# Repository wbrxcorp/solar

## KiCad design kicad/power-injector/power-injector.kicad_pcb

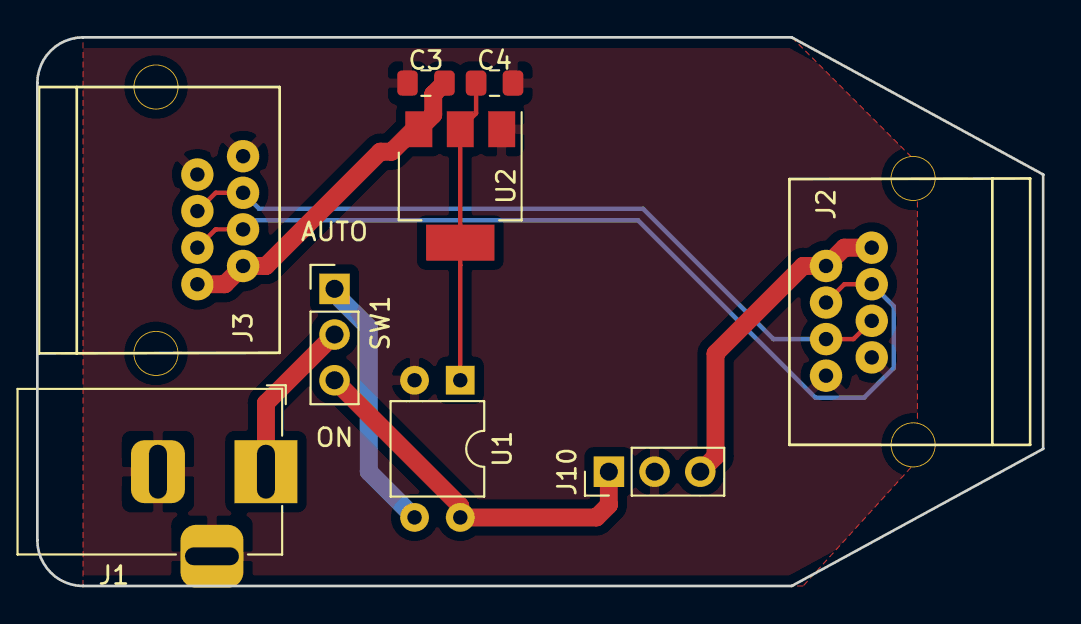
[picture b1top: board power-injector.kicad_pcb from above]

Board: 2 copper layers, 55.9 x 30.5 mm, 9 parts (0 on the bottom side), 9 nets.

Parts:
C3, C4: 0.1uF; C_0805_2012Metric_Pad1.15x1.40mm_HandSolder
J1: Barrel_Jack_Switch; BarrelJack_Horizontal
J2, J3: RJ45
J10: DCDC; PinHeader_1x03_P2.54mm_Vertical
SW1: SW_SPDT; PinHeader_1x03_P2.54mm_Vertical
U1: TLP222A; DIP-4_W7.62mm
U2: AMS1117-1.2; SOT-223-3_TabPin2

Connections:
/1V2: C4.1, U1.1, U2.2
/5V: J2.1, J2.2, J10.3
/A: J2.5, J2.6, J3.5, J3.6
/B: J2.3, J2.4, J3.3, J3.4
/VBATT: J10.1, SW1.3, U1.4
/VBATT_AUTO: SW1.1, U1.3
/VBATT_IN: J1.1, SW1.2
/VCTRLR: C3.1, J3.1, J3.2, U2.3
GND: C3.2, C4.2, J1.2, J1.3, J2.7, J2.8, J3.7, J3.8, J10.2, U1.2, U2.1

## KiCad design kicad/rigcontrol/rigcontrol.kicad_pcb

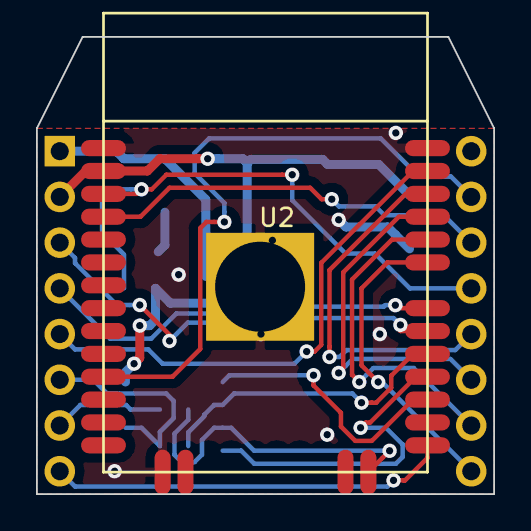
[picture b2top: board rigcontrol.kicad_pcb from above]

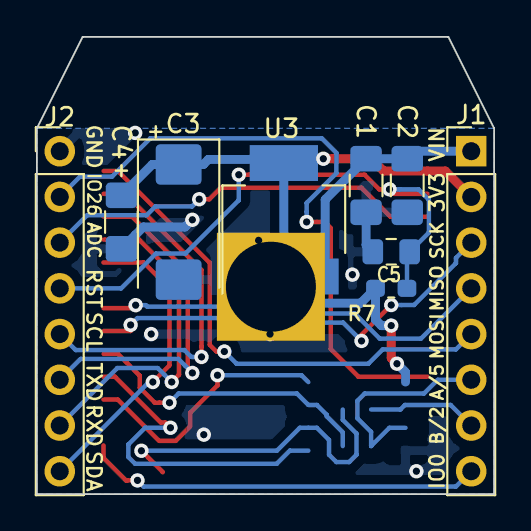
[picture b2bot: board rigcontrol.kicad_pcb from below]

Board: 2 copper layers, 25.4 x 25.4 mm, 10 parts (9 on the bottom side), 13 nets.

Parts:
C1, C2, C4: C; C_1206_3216Metric_Pad1.42x1.75mm_HandSolder
C3: C; CP_EIA-7343-15_Kemet-W_Pad2.25x2.55mm_HandSolder
C5: 1uF; C_0805_2012Metric_Pad1.15x1.40mm_HandSolder
J1, J2: Conn_01x08; PinHeader_1x08_P2.54mm_Vertical
R7: 10K; R_0603_1608Metric_Pad1.05x0.95mm_HandSolder
U2: ESP-WROOM-32; ESP32-WROOM
U3: AMS1117-3.3; SOT-223-3_TabPin2

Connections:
+3V3: C3.1, C4.1, J1.2, R7.1, U2.2, U3.2
GND: C1.2, C2.2, C3.2, C4.2, C5.2, J2.1, U2.1, U2.15, U2.38, U2.39, U3.1
IO0: J1.8, U2.25
IO26: J2.2, U2.11
MISO: J1.4, U2.31
MOSI: J1.5, U2.37
RST: C5.1, J2.4, R7.2, U2.3
RXD: J2.7, U2.34
SCK: J1.3, U2.30
SCL: J2.5, U2.36
SDA: J2.8, U2.33
TXD: J2.6, U2.35
VCC: C1.1, C2.1, J1.1, U3.3

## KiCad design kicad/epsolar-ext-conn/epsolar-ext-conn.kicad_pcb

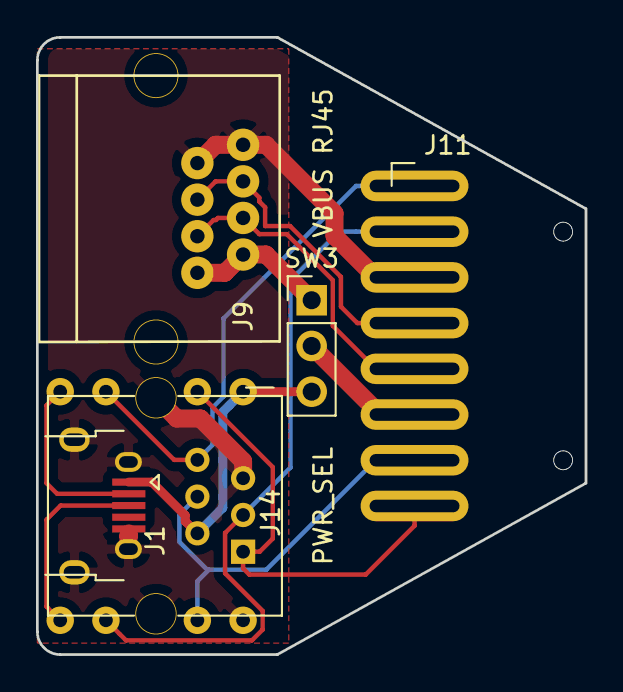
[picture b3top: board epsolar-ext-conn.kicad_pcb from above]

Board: 2 copper layers, 30.5 x 34.3 mm, 5 parts (0 on the bottom side), 12 nets.

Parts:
J1: USB_B_Micro; USB_Micro-B_Horizontal
J9: RJ45
J11: CONN; 8p_cable_holes
J14: USBSERIAL; usbserial
SW3: SW_SPDT; PinHeader_1x03_P2.54mm_Vertical

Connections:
/A: J9.5, J9.6, J11.4
/B: J9.3, J9.4, J11.5
/D+: J1.3, J14.7
/D-: J1.2, J14.8
/IO0: J11.1, J14.6
/RESET: J11.8, J14.1
/RXD: J11.2, J14.3
/TXD: J11.7, J14.4
/VBUS: J1.1, J14.2, SW3.3
/VCTRLR: J9.1, J9.2, SW3.1
/VIN: J11.6, SW3.2
GND: J1.5, J1.6, J9.7, J9.8, J11.3, J14.5

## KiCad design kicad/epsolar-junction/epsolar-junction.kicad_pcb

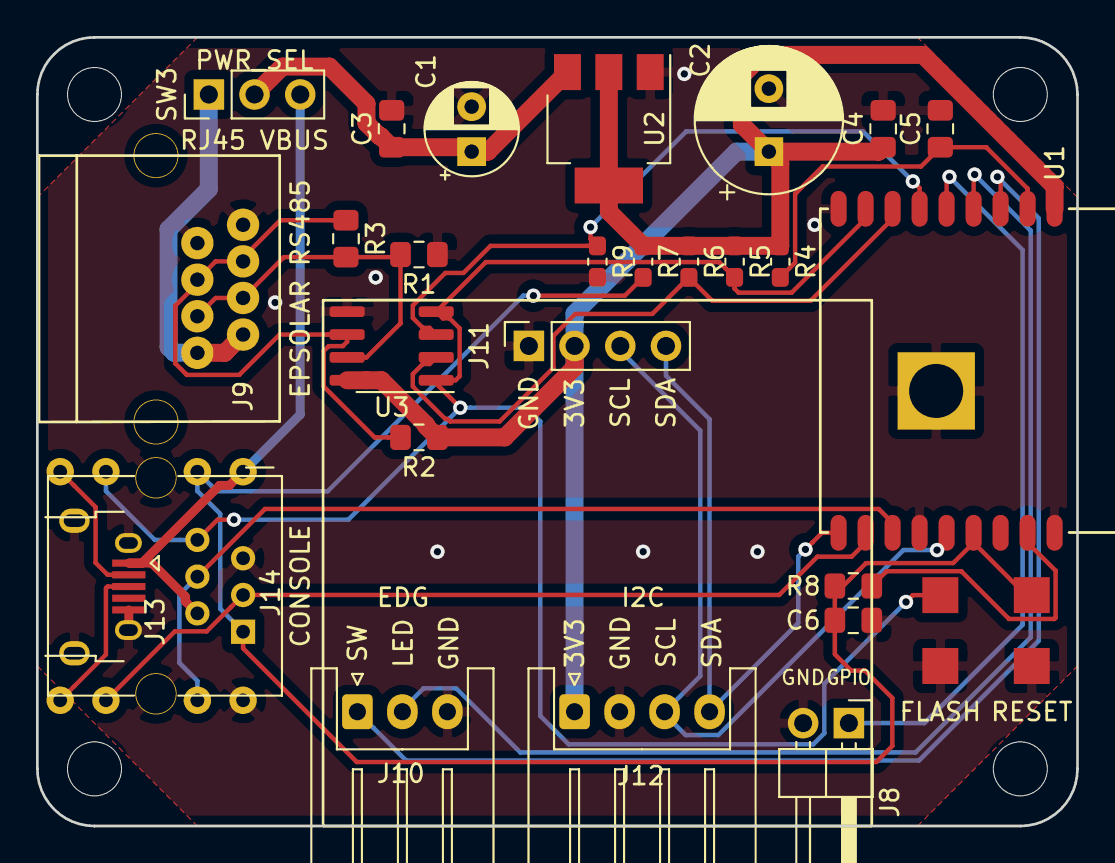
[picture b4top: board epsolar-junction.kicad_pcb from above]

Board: 2 copper layers, 57.8 x 43.8 mm, 28 parts (0 on the bottom side), 22 nets.

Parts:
C1: 100uF; CP_Radial_D5.0mm_P2.50mm
C2: 1000uF; CP_Radial_D8.0mm_P3.50mm
C3, C4, C5, C6: 0.1uF; C_0805_2012Metric_Pad1.15x1.40mm_HandSolder
J8: Conn_01x02; PinHeader_1x02_P2.54mm_Horizontal
J9: RJ45
J10: EDG; JST_XH_S3B-XH-A_1x03_P2.50mm_Horizontal
J11: DISPLAY; PinSocket_1x04_P2.54mm_Vertical
J12: I2C; JST_XH_S4B-XH-A_1x04_P2.50mm_Horizontal
J13: USB_B_Micro; USB_Micro-B_Horizontal
J14: USBSERIAL; usbserial
R1, R2: 20K; R_0805_2012Metric_Pad1.15x1.40mm_HandSolder
R3: 200; R_0805_2012Metric_Pad1.15x1.40mm_HandSolder
R4, R5, R6, R7, R9: 10K; R_0603_1608Metric_Pad1.05x0.95mm_HandSolder
R8: 470; R_0805_2012Metric_Pad1.15x1.40mm_HandSolder
SW1, SW2: SW_Push; tactile_switch_smd_4x3mm_2p
SW3: SW_SPDT; PinHeader_1x03_P2.54mm_Vertical
U1: ESP-13-WROOM-02
U2: AMS1117-3.3; SOT-223-3_TabPin2
U3: MAX3485; SOIC-8_3.9x4.9mm_P1.27mm

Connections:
/3V3: C2.1, C4.1, J11.2, J12.1, R2.1, R4.1, R5.1, R6.1, R7.1, U1.1, U2.2, U3.8
/A: J9.5, J9.6, R2.2, R3.1, U3.6
/B: J9.3, J9.4, R1.2, R3.2, U3.7
/D+: J13.3, J14.7
/D-: J13.2, J14.8
/EDG_LED: J10.2, U1.4
/EDG_SW: J10.1, U1.3
/EN: C5.1, R4.2, U1.2
/GPIO: J8.1, U1.5
/IO0: J14.6, R5.2, SW2.1, U1.8, U3.1, U3.4
/IO2: R6.2, U1.7, U3.2
/IO15: R9.1, U1.6, U3.3
/RESET: C6.1, J14.1, R7.2, R8.2, SW1.1, U1.15
/RXD: J14.3, U1.11
/SCL: J11.3, J12.3, U1.14
/SDA: J11.4, J12.4, U1.10
/TXD: J14.4, U1.12
/VBUS: J13.1, J14.2, SW3.3
/VCTRLR: J9.1, J9.2, SW3.1
/VIN: C1.1, C3.1, SW3.2, U2.3
/WAKE: R8.1, U1.17
GND: C1.2, C2.2, C3.2, C4.2, C5.2, C6.2, J8.2, J9.7, J9.8, J10.3, J11.1, J12.2, J13.5, J13.6, J14.5, R1.1, R9.2, SW1.2, SW2.2, U1.9, U1.13, U1.18, U1.PAD, U2.1, U3.5

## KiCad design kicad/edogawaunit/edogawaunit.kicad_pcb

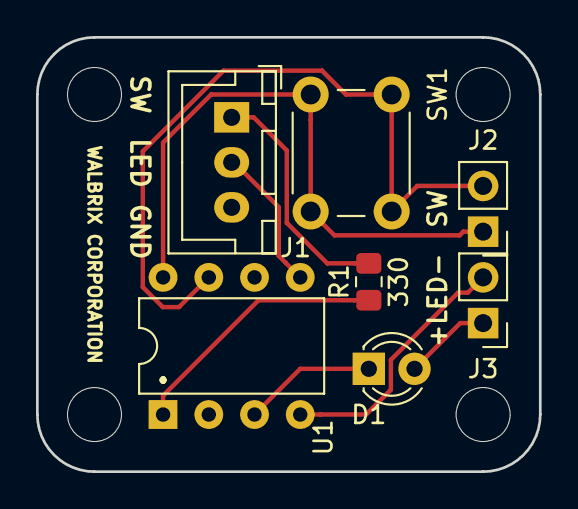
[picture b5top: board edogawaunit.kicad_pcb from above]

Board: 2 copper layers, 27.9 x 24.1 mm, 7 parts (0 on the bottom side), 9 nets.

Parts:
D1: LED; LED_D3.0mm
J1: Conn_01x03; JST_XH_B03B-XH-A_1x03_P2.50mm_Vertical
J2, J3: Conn_01x02; PinHeader_1x02_P2.54mm_Vertical
R1: 330; R_0805_2012Metric_Pad1.15x1.40mm_HandSolder
SW1: SW_Push; SW_PUSH_6mm
U1: TLP222A-2; DIP-8_W7.62mm

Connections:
/LEDMINUS: J3.2, U1.4
/LEDPLUS: D1.2, J3.1
/LED_IN: J1.2, U1.5
/SW1: J2.1, SW1.2, U1.8
/SW2: J2.2, SW1.1, U1.7
/SW_OUT: J1.1, R1.2
GND: J1.3, U1.2, U1.6
unnamed: D1.1, U1.3
unnamed: R1.1, U1.1

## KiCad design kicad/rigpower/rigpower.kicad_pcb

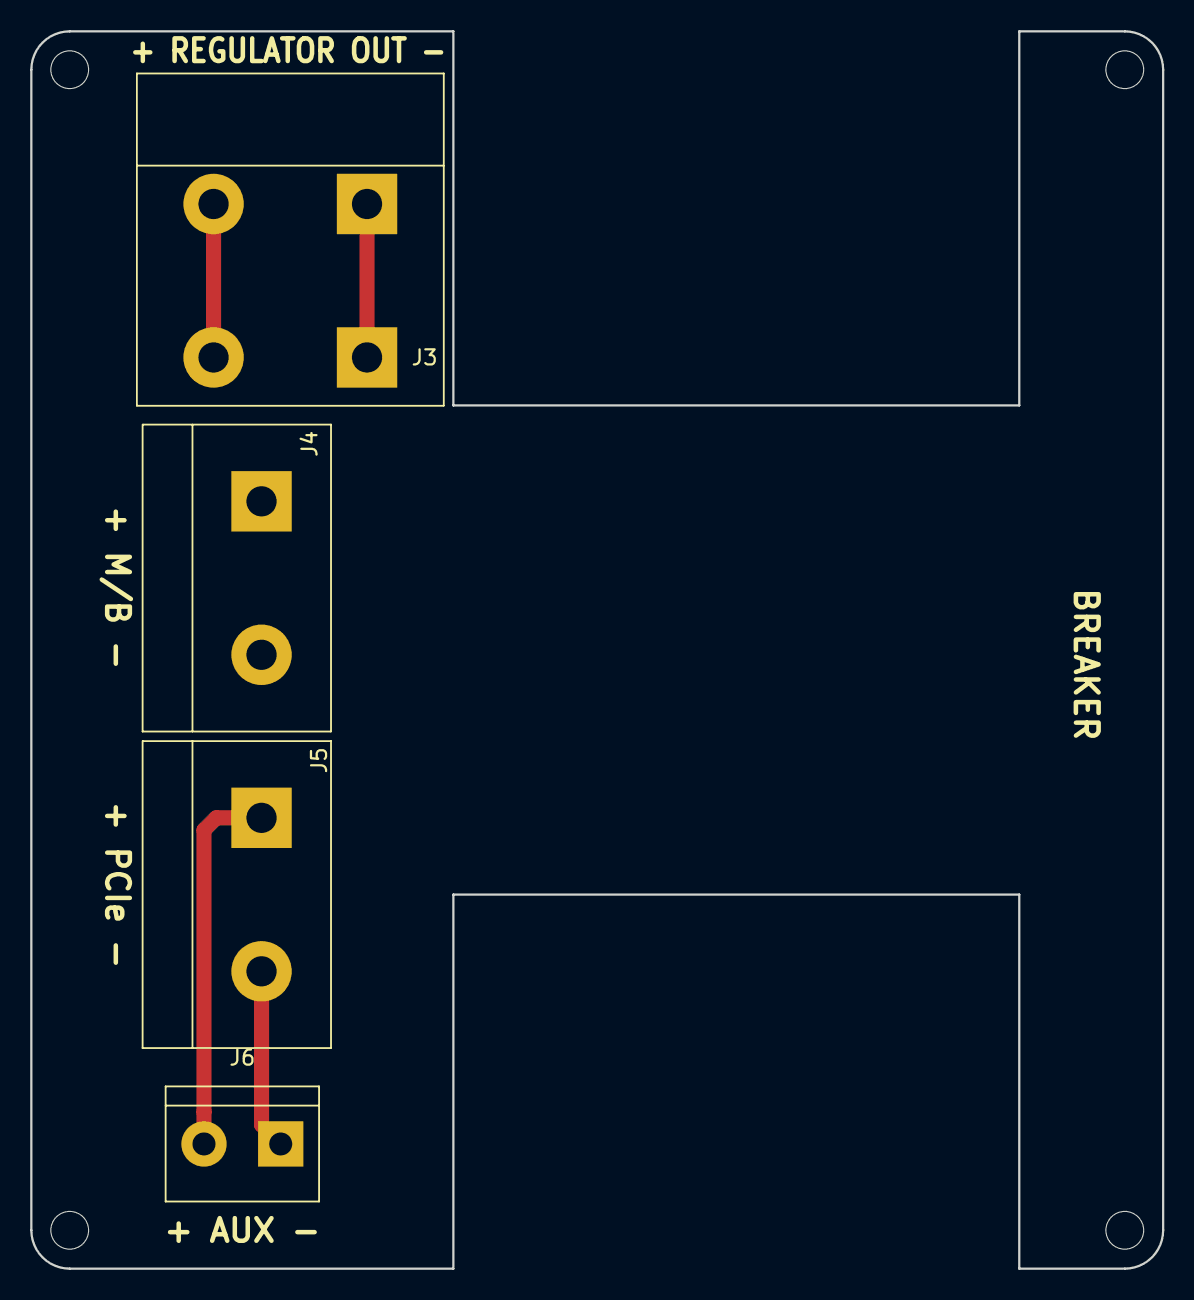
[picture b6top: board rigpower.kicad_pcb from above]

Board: 2 copper layers, 74.9 x 81.9 mm, 4 parts (0 on the bottom side), 2 nets.

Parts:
J3: Conn_01x02; TerminalBlock_P10.16mm
J4, J5: Conn_01x02; TerminalBlock_P9.5mm
J6: Conn_01x02; TerminalBlock_bornier-2_P5.08mm

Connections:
unnamed: J5.1, J6.2
unnamed: J5.2, J6.1

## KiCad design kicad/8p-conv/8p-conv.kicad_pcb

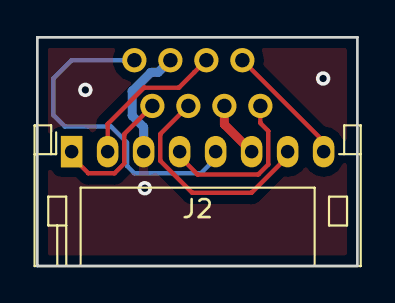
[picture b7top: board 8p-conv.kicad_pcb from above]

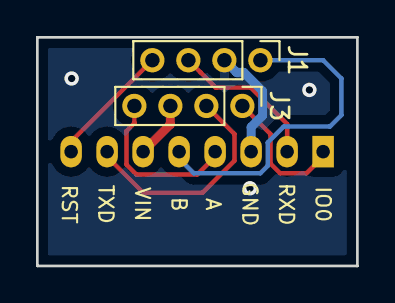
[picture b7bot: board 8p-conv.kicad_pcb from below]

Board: 2 copper layers, 17.8 x 12.7 mm, 3 parts (2 on the bottom side), 8 nets.

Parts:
J1, J3: Conn_01x04; PinHeader_1x04_P2.00mm_Vertical
J2: Conn_01x08; JST_PH_S8B-PH-K_1x08_P2.00mm_Horizontal

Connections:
/A: J2.4, J3.4
/B: J1.1, J2.5
/GND: J1.2, J2.3
/IO0: J2.1, J3.1
/RST: J1.4, J2.8
/RXD: J1.3, J2.2
/TXD: J2.7, J3.2
/VIN: J2.6, J3.3

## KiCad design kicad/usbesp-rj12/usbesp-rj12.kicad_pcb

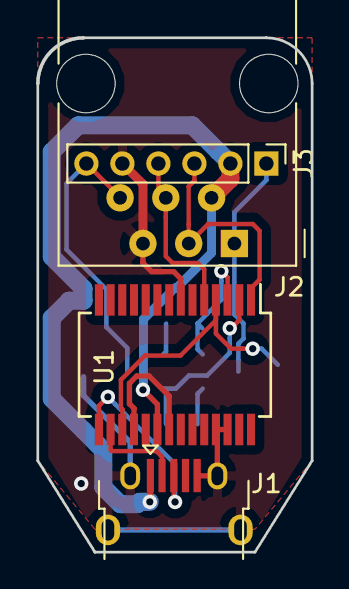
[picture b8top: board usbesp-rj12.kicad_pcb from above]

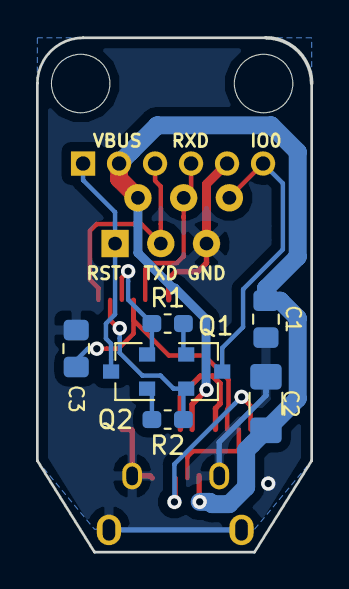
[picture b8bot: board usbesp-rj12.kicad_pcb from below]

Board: 2 copper layers, 15.2 x 28.6 mm, 11 parts (7 on the bottom side), 13 nets.

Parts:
C1, C3: 0.1uF; C_0805_2012Metric_Pad1.15x1.40mm_HandSolder
C2: 10uF; C_1206_3216Metric_Pad1.42x1.75mm_HandSolder
J1: USB_B_Micro; USB_Micro-B_Horizontal
J2: RJ12; RJ12_Amphenol_54601
J3: Conn_01x06; PinHeader_1x06_P2.00mm_Vertical
Q1, Q2: S9013; SOT-23
R1, R2: 10K; R_0603_1608Metric_Pad1.05x0.95mm_HandSolder
U1: FT232RL; SSOP-28_5.3x10.2mm_P0.65mm

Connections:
/3v3: C3.1, U1.4, U1.17
/DTR: Q1.2, R2.1, U1.2
/IO0: J2.6, J3.6, Q1.3
/RESET: J2.1, J3.1, Q2.3
/RTS: Q2.2, R1.1, U1.3
/RXD: J2.4, J3.4, U1.5
/TXD: J2.3, J3.3, U1.1
/USBDM: J1.2, U1.16
/USBDP: J1.3, U1.15
/VBUS: C1.1, C2.1, J1.1, J2.2, J3.2, U1.20
GND: C1.2, C2.2, C3.2, J1.5, J1.6, J2.5, J3.5, U1.7, U1.18, U1.21, U1.25, U1.26
unnamed: Q1.1, R1.2
unnamed: Q2.1, R2.2

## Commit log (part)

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2017-08-15 initial
2017-08-15 add poll script
2017-08-18 pyeptracer code adopted
2017-08-18 save to db functionality added
2017-08-18 ignore .txt files
2017-08-18 change 5min avg line color
2017-08-19 legend added
2017-08-21 possibility to specify output path
2017-08-24 set battery voltage y axis limits
2017-08-25 adjust legend text
2017-08-25 pymodbus adopted
2017-08-26 adjust battery voltage yaxis upper limit
2017-08-26 email_graph script added
2017-09-26 schema changed to store loads
2017-09-26 graph improved
2017-09-26 setparam utility added
2017-09-26 add 12v line
2017-10-06 htdocs added
2017-10-06 charset specified
2017-10-07 show usdjpy
2017-10-08 use yahoo api to get jpyusd
2017-10-09 a mandatory arg was missing
2017-10-13 coins.json format changed
2017-10-14 refresh functionality implemented
2017-10-14 btc price added
2017-10-14 refresh improved
2017-10-14 IoT server
2017-10-15 faster query using temporary table
2017-10-15 MySQL can't perform self join on temporary table (MariaDB can, though)
2017-10-15 Using temporary table makes things worse on MySQL
2017-10-15 amend 022f771
2017-10-15 Efficiency added
2017-10-17 arduino code added
2017-10-23 Send data from EPSolar Tracer via WiFi
2017-10-23 store received data
2017-10-23 reduce data by skipping panel input voltage = 0
2017-10-23 improved
2017-10-26 node paramater support
2017-10-26 controller setting WIP
2017-10-26 set charge controller RTC according to time suggested by server
2017-10-27 webcam capture script added
2017-10-28 outlet power control config reset pin
2017-10-28 temperature graph added
2017-10-29 millis should be unsigned
2017-10-30 add session id to protocol
2017-10-30 turn on main power before atx power
2017-10-30 baud rate is 115200 when mega
2017-10-31 add power on/off schedule utility
2017-10-31 change the way to preserve storage
2017-10-31 amend last commit
2017-10-31 fix typo
2017-10-31 some effeiency improvements
2017-11-01 make response message single packet
2017-11-01 int size oops
2017-11-02 inputregister class was corrupting
2017-11-02 reading device info support
2017-11-03 code cleanups
2017-11-03 ability to change nodename
2017-11-03 stop using large buffer to preserve memory
2017-11-03 cleanup
2017-11-04 functionality to control switches according to battery voltage
2017-11-05 use 1 minute average for determiing battery voltage
2017-11-06 ifdef instead of if
2017-11-06 ESP32 WIP
2017-11-06 network connection implemented
2017-11-06 Use temporary hostname instead of nodename
2017-11-08 ESP32 version under development
2017-11-08 hex print debug functionality
2017-11-08 explicitly set load controlling mode
2017-11-09 put pv power on camera pic
2017-11-09 decrease max retry reading modbus at init
2017-11-09 power.py is now set_value.py
2017-11-11 capability to change baud rate in wifi direct mode
2017-11-11 correct 0W data decimation logic
2017-11-11 add uncompensated battery voltage field
2017-11-11 consider bv compensation when control power using battery voltage
2017-11-11 add charging status field
2017-11-11 use "battery temperature compensation voltage" instead of "uncompensanted battery temperature"
2017-11-12 add itemp(temparature inside case) field
2017-11-12 create poweroff_pw() function
2017-11-13 care for new node
2017-11-13 finally got it work
2017-11-13 insert delay to save cpu time
2017-11-23 RS485 leading zero problem solved by updating esp-idf
2017-11-26 acquire lock during capture
2017-12-23 preserve power
2017-12-30 capability to set jpeg quality
2018-01-13 migrate to batch json download scheme
2018-01-13 minor mistake
2018-01-13 change place to put days left
2018-01-13 fix days left calculation
2018-01-19 worker list
2018-01-19 stupid bug
2018-01-20 fix approximated_earnings API URL
2018-02-01 correct condition
2018-02-01 coins.cgi moved to update.py
2018-02-01 add products table
2018-02-01 out of stock product
2018-02-17 support etn on mph
2018-02-17 improve view
2018-03-10 Turn Coil #6 on at the startup. Arduino Mega version (ESP32 to be done)
2018-03-10 apply last change to esp32 too
2018-03-22 uart_num should be variable instead of constant
2018-03-30 Use default instance of MDNSResponder
2018-03-31 Use UART1 instead of UART2
2018-03-31 stop using magic number
2018-04-01 Support ESP8266(TBD)
2018-04-01 Remove PW2 support from ESP8266
2018-04-01 Adjust pin assignment for D1 mini series
2018-04-01 Correct SoftwareSerial I/O pins
2018-04-01 Use modem-sleep correctly
2018-04-02 light sleep for esp8266
2018-04-02 modem_sleep instead of light_sleep
2018-04-02 remove F() macro (It's still efficient in ESP8266, though)
2018-04-03 Re-implement LineBuffer using Arduino's String class
2018-04-03 adjust pin definitions
2018-04-04 capability to remap pins for edogawa unit
2018-04-04 use LED_BUILTIN
2018-04-05 forget SPI. need to move cmdline only mode pin to D8 (GPIO5 in ESP32)
2018-04-08 add display support
2018-04-09 code refoctored
2018-04-09 fix something left unreplaced
2018-04-10 done more refactoring
2018-04-11 add debug mode
2018-04-14 don't automatically power on when node connects
2018-04-14 network code refactored
2018-04-14 fix esp8266
2018-04-14 network fixed
2018-04-15 epsolar refactored
2018-04-15 modbus retry properly
2018-04-16 show build date at startup
2018-04-16 add reboot command
2018-04-16 Turn display off when reboot
2018-04-17 buffer for message can be shorter than necessary. use printf instead sprintf
2018-04-29 see last battery voltage when to decide if store data
2018-05-04 Use D0 as RS485 RTS pin EdogawaUnit 2 added
2018-05-11 Arduino Mega support
2018-06-06 turning off pw2 fix
2018-06-10 always update *.user.json
2018-06-12 remove products table
2018-06-15 use new fixer.io api
2018-06-17 profit/hashrate evaluation
2018-06-27 use MIMEImage instead of MIMEApplication
2018-07-10 modbus message improved
2018-07-10 rotate something on OLED while connecting to WiFi
2018-09-07 parts selected
2018-09-07 donw some work
2018-09-07 create order zip for elecrow
2018-09-08 migrated to KiCad 5
2018-09-08 add new pcb
2018-09-09 breakout-board type variant added
2018-09-09 all done probably
2018-09-09 fix erratta
2018-09-09 done some optimization
2018-09-09 more gnd optimization
2018-09-10 base board done
2018-09-10 base board does not need esp8266
2018-09-10 improve elecrow script
2018-09-10 rj45 update
2018-09-10 pad shape change
2018-09-11 add SOT package module
2018-09-15 add ams1117
2018-09-15 correct pad shape
2018-09-18 was about to produce holeless PCB
2018-09-19 Capacitor for EN pin added
2018-09-19 correct text placement
2018-09-19 font size adjusted
2018-09-20 add vias to enlarge gnd pad
2018-09-22 USB I/Fs added
2018-09-22 moved a text on the board
2018-09-22 size annotated
2018-09-29 server functionality added. EEPROM layout changed.
2018-09-30 Edogawa Unit PCB added
2018-09-30 esp485 base board
2018-09-30 migrated to single wire half duplex method
2018-10-05 pinouts for OLED module and external devices changed
2018-10-05 added 4 layers pcb
2018-10-12 setTransmitEnablePin is useless
2018-10-17 make ESP8266 dedicated to one wire half duplex
2018-10-17 schematic was wrong
2018-10-17 Always disable interrupt during TX operation
2018-10-17 constant like naming
2018-10-17 trivial (but critical for ESP32) corrections
2018-10-18 re-add delay(1) to prevent being rebooted unexpectedly
2018-10-20 EdogawaUnit shrinked
2018-10-22 sleep supported
2018-10-22 MySQL 5.7 compatiblity
2018-10-30 non-interrupt driven modbus communication implemented and not it's dedicated to esp8266
2018-10-31 put resistor between IO16 and RESET
2018-10-31 esp485 2layers PCB refined
2018-11-04 feed WDT not to be bitten
2018-11-04 remove switches
2018-11-04 ESP-12F breakout board bump
2018-11-04 sleep threshold changed
2018-11-07 esp32 version TBD
2018-11-08 esp485-32 done
2018-11-09 get esp32 back
2018-11-10 change sleep condition
2018-11-10 control RS485 DE/!RE separately to save power
2018-11-10 board width was a bit short
2018-11-11 migrated to RS485 sleep capable design
2018-11-11 replace display library
2018-11-14 edogawamaster added
2018-11-16 output data to serial as well
2018-11-24 RS485 comm adjusted
2018-11-24 8pin conversion board
2018-11-24 pcb setting
2018-11-24 extract rs485 from epsolar
2018-11-25 make epsolar not to inherit rs485modbus
2018-11-29 enable sleep mode flag removed(always enabled)
2018-12-01 NiseTracer implemented
2018-12-01 silk erratta corrected
2018-12-02 usage of rtc data improved
2018-12-02 improve nisetracer
2018-12-04 termination resistor added
2018-12-04 esp485-base-bb added
2018-12-08 wake resister silk corrected from 1k to 470
2018-12-08 resistor value corrected
2018-12-09 don't sleep when load > 0
2018-12-12 RS485Modbus to use hardware UART with ESP32
2018-12-14 edogawamaster converted to esp8266/esp32
2018-12-15 ST7789 TFT Driver added
2018-12-17 thermometer function merged
2018-12-17 TFT ESP32 support
2018-12-17 edogawa_master supports tft
2018-12-17 disable TFT when running edogawa_master on ESP8266
2018-12-24 sleep support
2018-12-25 should use print instead of write to send number in text
2018-12-26 Don't send sleep corresponding to non-DATA message
2018-12-30 server to support ESP32
2018-12-31 conversion board for cheap rj45 connector
2019-01-03 check existence of INA219 before begin
2019-01-03 typo
2019-01-03 upload command for 2MB chips
2019-01-04 2 pcbs added
2019-01-04 use Agg driver when X is not available
2019-01-06 get wifi rssi value
2019-01-10 ammeter to print values on display
2019-01-12 contrast setting added
2019-01-12 nisetracer does not need wifi
2019-01-12 Show CPU freq at the boot time Slave operation mode added(TBD)
2019-01-14 slave improved
2019-01-18 universal pcb for voltage regulator
2019-01-18 ability to change slave id
2019-01-24 usbesp-rj12 added
2019-01-24 rj12-54601 added
2019-01-24 rj12-54601-breakout added
2019-01-28 add USB add-on add-on board support
2019-02-19 USB MicroB update
2019-02-20 PCB improved
2019-02-20 immediately send message after wake-up from deep sleep
2019-02-22 usbesp-rj12 moved to other project
2019-02-23 SPI clock must be <= 60MHz
2019-02-23 support CCS811 gas sensor
2019-02-23 show eCO2 in tft
2019-02-25 provide environmental data for ccs811
2019-03-04 regulator removed
2019-03-14 show sdk versions when boot
2019-03-14 8p-PH conversion board for esp32-devboard
2019-03-15 add led operation to thermometer
2019-03-27 remove unnecesary linefeed
2019-04-04 rigpower added
2019-04-08 drawing improved
2019-04-20 epsolar-junction added
2019-04-20 gbr files naming changed in kicad 5.1?
2019-04-20 remove some thermal relieves
2019-04-21 silk text changed
2019-04-24 layout change
2019-04-24 add some error checks
2019-04-25 Use INA219 even in normal operation mode
2019-04-25 Adjust where to begin INA219
2019-04-26 Restart when connection not established with several retries
2019-05-01 don't gear up when very hot
2019-05-01 force check request supported say "stay" when no need to perform gearchange
2019-05-03 battery soc(State of Charge) support
2019-05-04 add AUX series
2019-05-04 SoC support
2019-05-04 SoC fixed
2019-05-05 Watchdog mode added
2019-05-07 AUX wattage graph added
2019-05-13 add pw when evaluete expression
2019-06-01 fix missing separator
2019-06-26 rigpower renewal
2019-07-09 3S/6S li-ion battery support watchdog uses also io2 to make esp-1 usable
2019-07-10 support graph for 3S/6S battery
2019-07-12 7S support
2019-08-02 adjust 3/6/7S battery charging voltages
2019-08-14 sleep longer when battery is low
2019-08-18 voltage settings for 3S/6S adjusted
2019-08-20 PCBs update
2019-09-09 rigcontrol(TBD) added
2019-09-17 adjust li-ion voltage again
2019-09-20 Temperature compensation coefficient must be zero for li-ion batteries
2019-09-21 adjust float charging voltage
2019-10-22 psuedo battery type=6(LiFePO4) added
2019-11-19 power-injector added
2020-03-18 show more info when received DNS-SD response
2020-07-31 specify ip stack
2021-05-10 add mmu parameter
2022-04-14 New esp8266 code added
2022-04-15 implemented all necessary features
2022-04-15 mutex lock removed for esp8266
2022-04-16 country setting support (to workaround ESP8266 firmware bug)
2022-04-30 change location of initializing tcpip adapter
2022-04-30 .txt file is necessary for esp-idf project
